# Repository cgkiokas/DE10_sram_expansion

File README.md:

# DE10 SRAM expansion board 
An SRAM expansion board for terasic DE-10 Nano board, with additional flight controller sensors.
Developed to accompany a DE-10 Nano board as a drone flight controller, using [T-CREST's Patmos](https://github.com/t-crest/patmos) processor. 

## Features
* 1Mx32bit SRAM
* 2 x 6-axis IMUs
* Magnetometer
* Barometer
* FTDI for UART output
* 7 GPIO Pins

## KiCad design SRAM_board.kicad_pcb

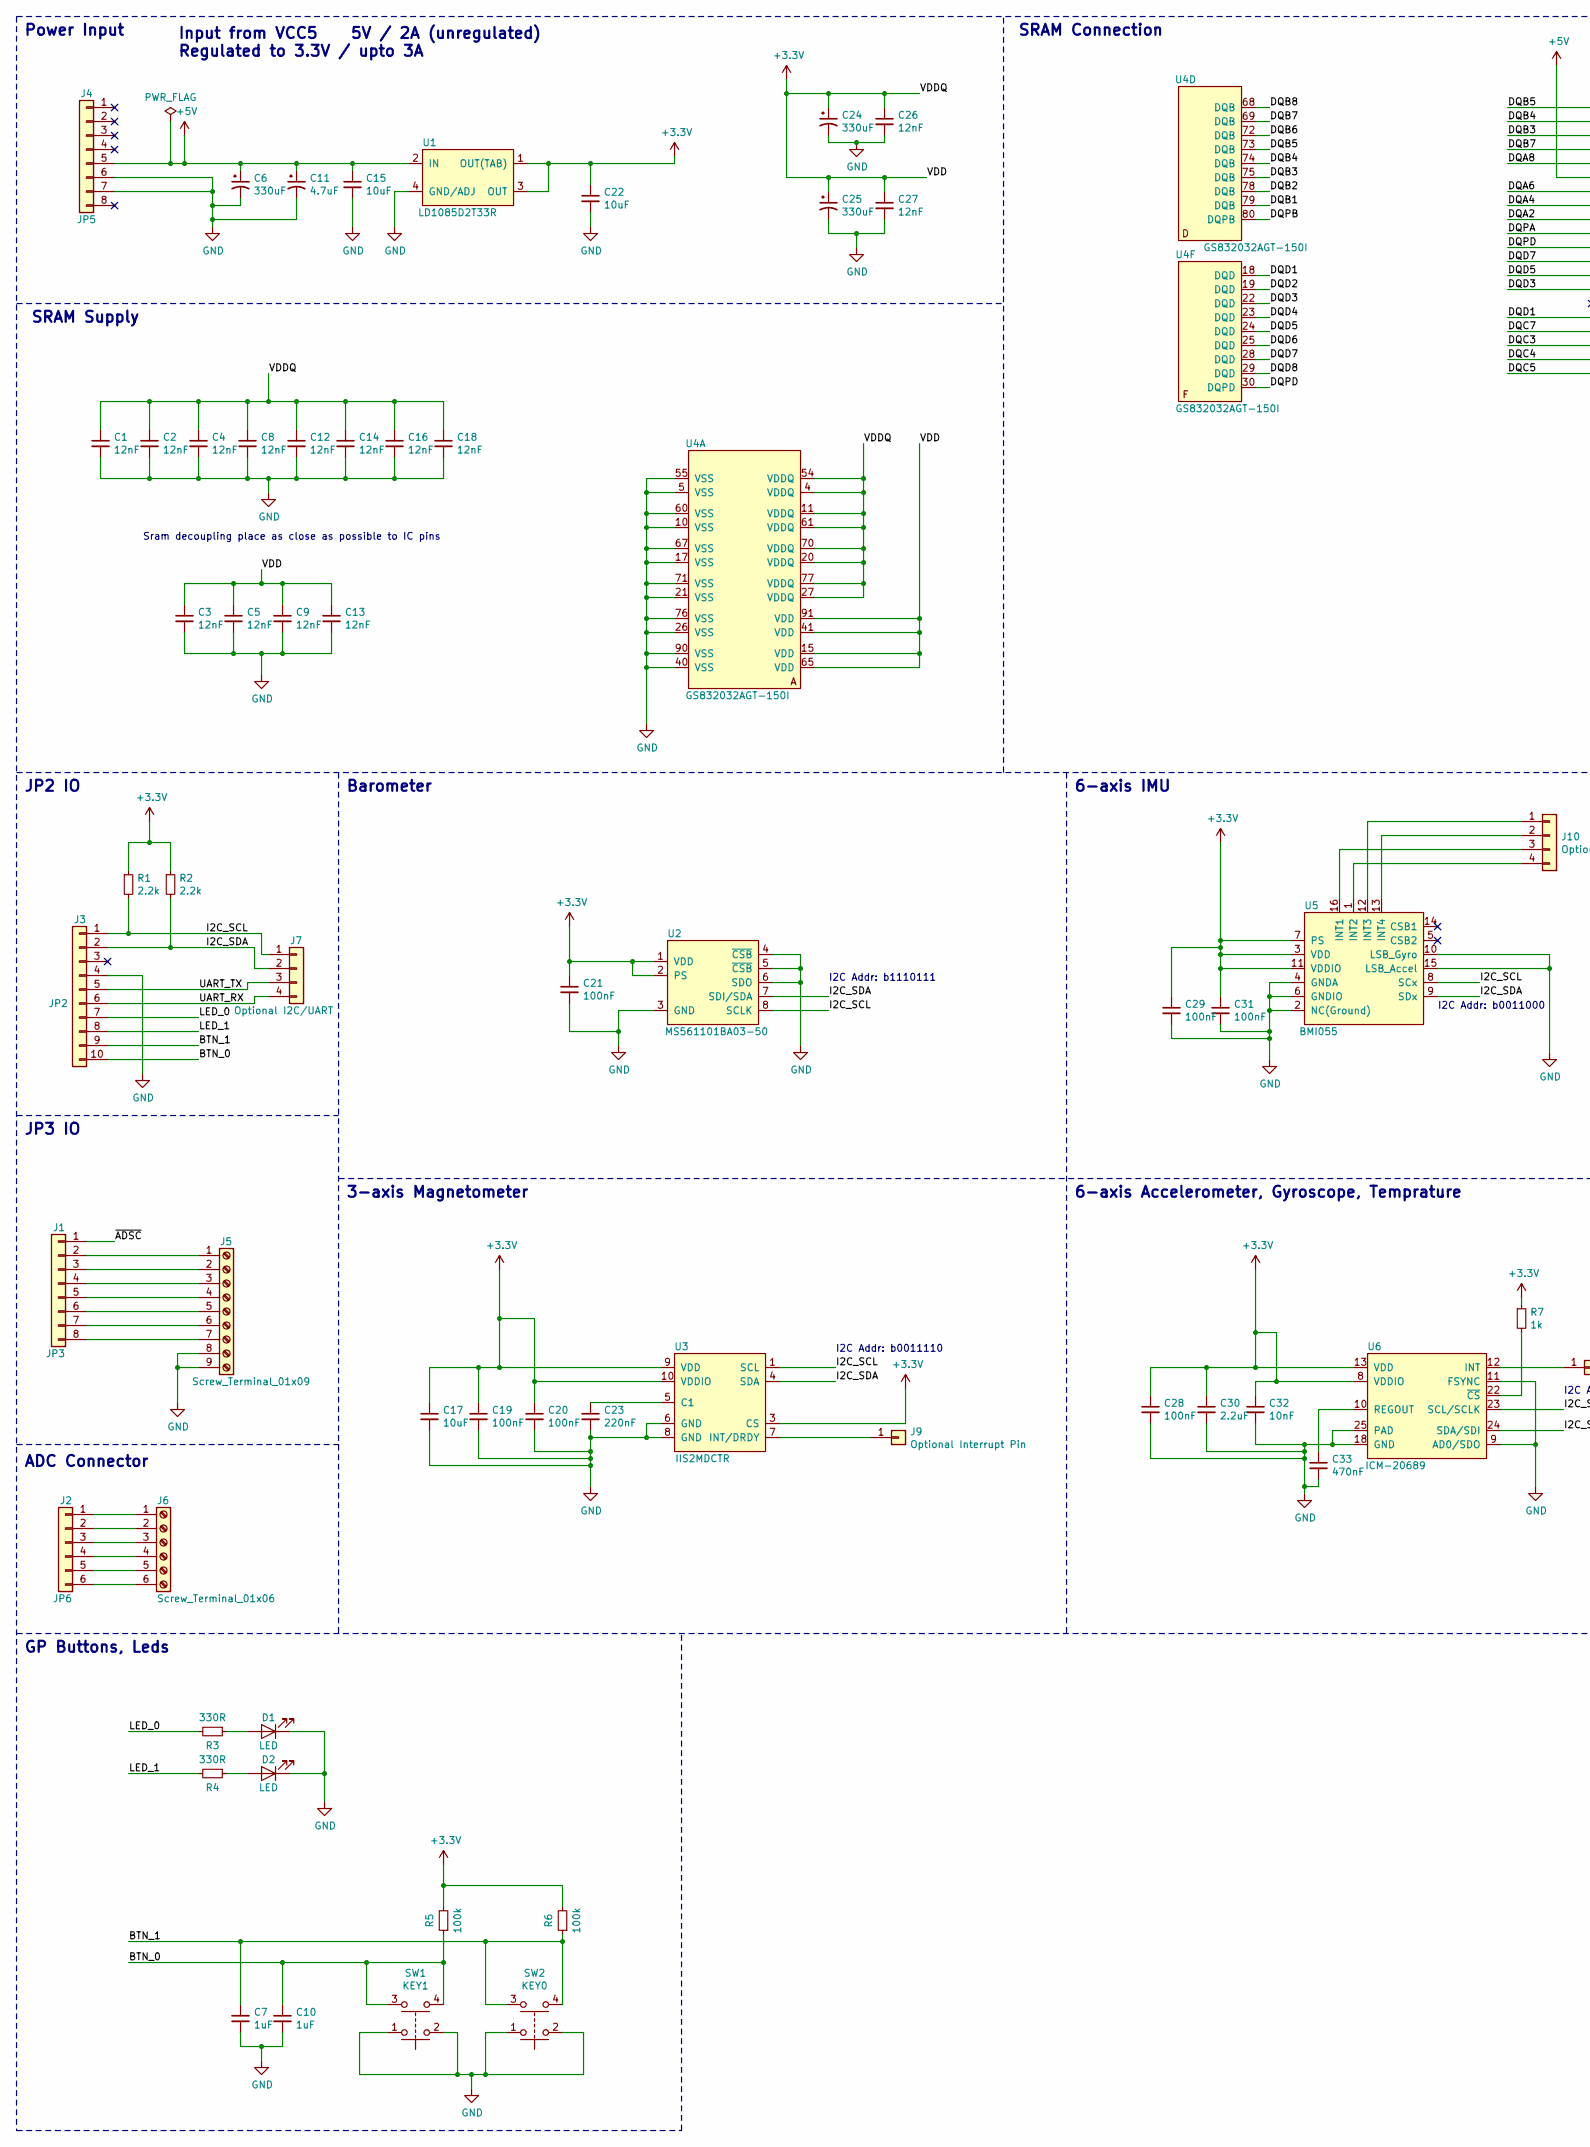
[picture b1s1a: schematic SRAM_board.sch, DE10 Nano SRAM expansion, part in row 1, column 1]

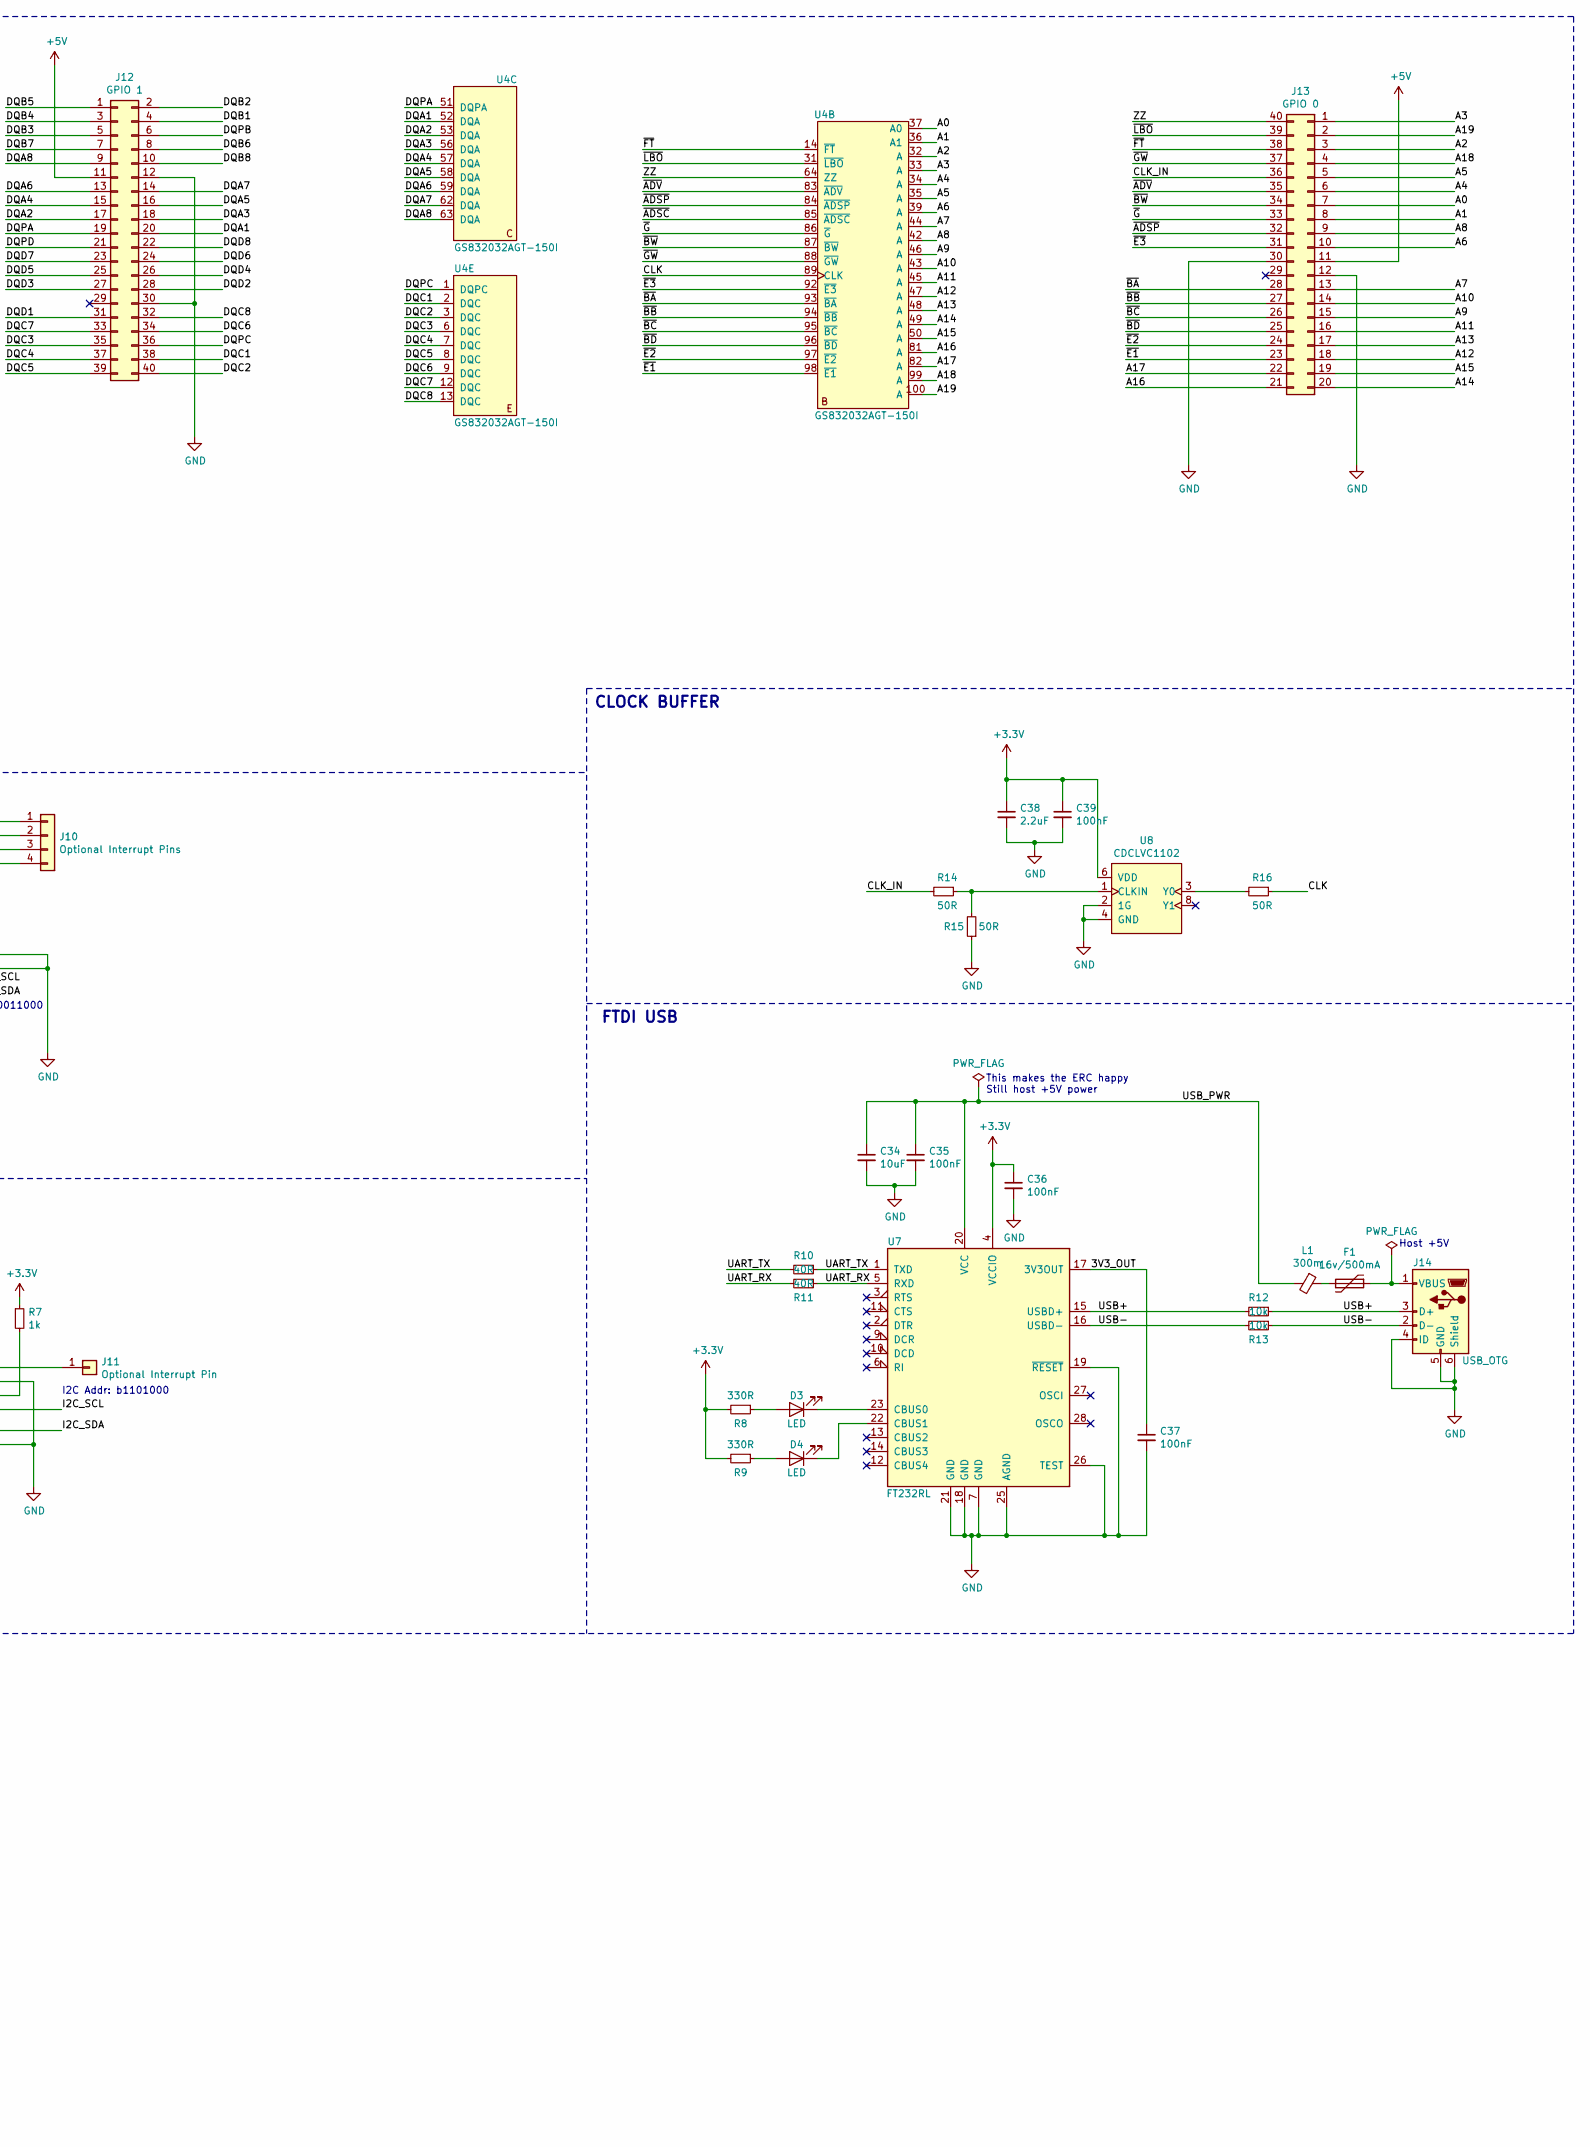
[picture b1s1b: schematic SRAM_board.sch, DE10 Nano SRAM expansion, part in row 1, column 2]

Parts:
C1, C2, C3, C4, C5, C8, C9, C12, C13, C14, C16, C18, C26, C27: 12nF; C_1206_3216Metric_Pad1.42x1.75mm_HandSolder
C6, C24, C25: 330uF; CP_Radial_D6.3mm_P2.50mm
C7, C10: 1uF; C_1206_3216Metric_Pad1.42x1.75mm_HandSolder
C11: 4.7uF; CP_Elec_4x5.8
C15, C17, C22, C34: 10uF; C_1206_3216Metric_Pad1.42x1.75mm_HandSolder
C19, C20, C21, C28, C29, C31, C35, C36, C37, C39: 100nF; C_1206_3216Metric_Pad1.42x1.75mm_HandSolder
C23: 220nF; C_1206_3216Metric_Pad1.42x1.75mm_HandSolder
C30, C38: 2.2uF; C_1206_3216Metric_Pad1.42x1.75mm_HandSolder
C32: 10nF; C_1206_3216Metric_Pad1.42x1.75mm_HandSolder
C33: 470nF; C_1206_3216Metric_Pad1.42x1.75mm_HandSolder
D1, D2, D3, D4: LED; LED_1206_3216Metric_Pad1.42x1.75mm_HandSolder
F1: 16v/500mA; Fuse_1206_3216Metric_Pad1.42x1.75mm_HandSolder
J1: JP3; PinHeader_1x08_P2.54mm_Vertical
J2: JP6; PinHeader_1x06_P2.54mm_Vertical
J3: JP2; PinHeader_1x10_P2.54mm_Vertical
J4: JP5; PinHeader_1x08_P2.54mm_Vertical
J5: Screw_Terminal_01x09; Screw_Terminal_1x09_2.54'_pitch
J6: Screw_Terminal_01x06; Screw_Terminal_1x06_2.54'_pitch
J7: Optional I2C/UART; PinHeader_1x04_P2.54mm_Vertical
J9, J11: Optional Interrupt Pin; PinHeader_1x01_P2.54mm_Vertical
J10: Optional Interrupt Pins; PinHeader_1x04_P2.54mm_Vertical
J12: GPIO 1; PinHeader_2x20_P2.54mm_Vertical
J13: GPIO 0; PinHeader_2x20_P2.54mm_Vertical
J14: USB_OTG; FCI_10118193_0001LF
L1: 300m; L_1206_3216Metric_Pad1.42x1.75mm_HandSolder
R1, R2: 2.2k; R_1206_3216Metric_Pad1.42x1.75mm_HandSolder
R3, R4, R8, R9: 330R; R_1206_3216Metric_Pad1.42x1.75mm_HandSolder
R5, R6: 100k; R_1206_3216Metric_Pad1.42x1.75mm_HandSolder
R7: 1k; R_1206_3216Metric_Pad1.42x1.75mm_HandSolder
R10, R11: 40R; R_1206_3216Metric_Pad1.42x1.75mm_HandSolder
R12, R13: 10k; R_1206_3216Metric_Pad1.42x1.75mm_HandSolder
R14, R15, R16: 50R; R_1206_3216Metric_Pad1.42x1.75mm_HandSolder
SW1: KEY1; LL3301NF065QG
SW2: KEY0; LL3301NF065QG
U1: LD1085D2T33R
U2: MS561101BA03-50
U3: IIS2MDCTR; LGA-12_2x2mm_P0.5mm
U4: GS832032AGT-150I; PQFP-100_14x20mm_P0.65mm
U5: BMI055
U6: ICM-20689
U7: FT232RL; SSOP-28_5.3x10.2mm_P0.65mm
U8: CDCLVC1102; SOIC-8

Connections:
+3V3: C1.1, C2.1, C3.1, C4.1, C5.1, C8.1, C9.1, C12.1, C13.1, C14.1, C16.1, C17.1, C18.1, C19.1, C20.1, C21.1, C22.1, C24.1, C25.1, C26.1, C27.1, C28.1, C29.1, C30.1, C31.1, C32.1, C36.1, C38.1, C39.1, R1.1, R2.1, R5.2, R6.2, R7.1, R8.2, R9.2, U1.1 (OUT(TAB)), U1.3 (OUT), U2.1 (VDD), U2.2 (PS), U3.3 (CS), U3.9 (VDD), U3.10 (VDDIO), U4.4 (VDDQ), U4.11 (VDDQ), U4.15 (VDD), U4.20 (VDDQ), U4.27 (VDDQ), U4.41 (VDD), U4.54 (VDDQ), U4.61 (VDDQ), U4.65 (VDD), U4.70 (VDDQ), U4.77 (VDDQ), U4.91 (VDD), U5.3 (VDD), U5.7 (PS), U5.11 (VDDIO), U6.8 (VDDIO), U6.13 (VDD), U7.4 (VCCIO), U8.6 (VDD)
+5V: C6.1, C11.1, C15.1, J4.5, J12.11, J13.11, U1.2 (IN)
/3V3_OUT: C37.1, U7.17 (3V3OUT)
/A0: J13.7, U4.37 (A0)
/A1: J13.8, U4.36 (A1)
/A2: J13.3, U4.32 (A)
/A3: J13.1, U4.33 (A)
/A4: J13.6, U4.34 (A)
/A5: J13.5, U4.35 (A)
/A6: J13.10, U4.39 (A)
/A7: J13.13, U4.44 (A)
/A8: J13.9, U4.42 (A)
/A9: J13.15, U4.46 (A)
/A10: J13.14, U4.43 (A)
/A11: J13.16, U4.45 (A)
/A12: J13.18, U4.47 (A)
/A13: J13.17, U4.48 (A)
/A14: J13.20, U4.49 (A)
/A15: J13.19, U4.50 (A)
/A16: J13.21, U4.81 (A)
/A17: J13.22, U4.82 (A)
/A18: J13.4, U4.99 (A)
/A19: J13.2, U4.100 (A)
/BTN_0: C10.1, J3.10, R5.1, SW1.3, SW1.4
/BTN_1: C7.1, J3.9, R6.1, SW2.3, SW2.4
/CLK: R16.1, U4.89 (CLK)
/CLK_IN: J13.36, R14.2
/DQA1: J12.20, U4.52 (DQA)
/DQA2: J12.17, U4.53 (DQA)
/DQA3: J12.18, U4.56 (DQA)
/DQA4: J12.15, U4.57 (DQA)
/DQA5: J12.16, U4.58 (DQA)
/DQA6: J12.13, U4.59 (DQA)
/DQA7: J12.14, U4.62 (DQA)
/DQA8: J12.9, U4.63 (DQA)
/DQB1: J12.4, U4.79 (DQB)
/DQB2: J12.2, U4.78 (DQB)
/DQB3: J12.5, U4.75 (DQB)
/DQB4: J12.3, U4.74 (DQB)
/DQB5: J12.1, U4.73 (DQB)
/DQB6: J12.8, U4.72 (DQB)
/DQB7: J12.7, U4.69 (DQB)
/DQB8: J12.10, U4.68 (DQB)
/DQC1: J12.38, U4.2 (DQC)
/DQC2: J12.40, U4.3 (DQC)
/DQC3: J12.35, U4.6 (DQC)
/DQC4: J12.37, U4.7 (DQC)
/DQC5: J12.39, U4.8 (DQC)
/DQC6: J12.34, U4.9 (DQC)
/DQC7: J12.33, U4.12 (DQC)
/DQC8: J12.32, U4.13 (DQC)
/DQD1: J12.31, U4.18 (DQD)
/DQD2: J12.28, U4.19 (DQD)
/DQD3: J12.27, U4.22 (DQD)
/DQD4: J12.26, U4.23 (DQD)
/DQD5: J12.25, U4.24 (DQD)
/DQD6: J12.24, U4.25 (DQD)
/DQD7: J12.23, U4.28 (DQD)
/DQD8: J12.22, U4.29 (DQD)
/DQPA: J12.19, U4.51 (DQPA)
/DQPB: J12.6, U4.80 (DQPB)
/DQPC: J12.36, U4.1 (DQPC)
/DQPD: J12.21, U4.30 (DQPD)
/I2C_SCL: J3.1, J7.1, R1.2, U2.8 (SCLK), U3.1 (SCL), U5.8 (SCx), U6.23 (SCL/SCLK)
/I2C_SDA: J3.2, J7.2, R2.2, U2.7 (SDI/SDA), U3.4 (SDA), U5.9 (SDx), U6.24 (SDA/SDI)
/LED_0: J3.7, R3.2
/LED_1: J3.8, R4.2
/UART_RX: J3.6, J7.4, R11.1, R11.2, U7.5 (RXD)
/UART_TX: J3.5, J7.3, R10.1, R10.2, U7.1 (TXD)
/USB+: J14.3 (D+), R12.1, R12.2, U7.15 (USBD+)
/USB-: J14.2 (D-), R13.1, R13.2, U7.16 (USBD-)
/USB_PWR: C34.1, C35.1, L1.2, U7.20 (VCC)
/ZZ: J13.40, U4.64 (ZZ)
/~ADSC: J1.1, U4.85 (~ADSC)
/~ADSP: J13.32, U4.84 (~ADSP)
/~ADV: J13.35, U4.83 (~ADV)
/~BA: J13.28, U4.93 (~BA)
/~BB: J13.27, U4.94 (~BB)
/~BC: J13.26, U4.95 (~BC)
/~BD: J13.25, U4.96 (~BD)
/~BW: J13.34, U4.87 (~BW)
/~E1: J13.23, U4.98 (~E1)
/~E2: J13.24, U4.97 (~E2)
/~E3: J13.31, U4.92 (~E3)
/~FT: J13.38, U4.14 (~FT)
/~G: J13.33, U4.86 (~G)
/~GW: J13.37, U4.88 (~GW)
/~LBO: J13.39, U4.31 (~LBO)
GND: C1.2, C2.2, C3.2, C4.2, C5.2, C6.2, C7.2, C8.2, C9.2, C10.2, C11.2, C12.2, C13.2, C14.2, C15.2, C16.2, C17.2, C18.2, C19.2, C20.2, C21.2, C22.2, C23.2, C24.2, C25.2, C26.2, C27.2, C28.2, C29.2, C30.2, C31.2, C32.2, C33.2, C34.2, C35.2, C36.2, C37.2, C38.2, C39.2, D1.1 (K), D2.1 (K), J3.4, J4.6, J4.7, J5.8, J5.9, J12.12, J12.30, J13.12, J13.30, J14.4 (ID), J14.5 (GND), J14.6 (Shield), R15.1, SW1.1, SW1.2, SW2.1, SW2.2, U1.4 (GND/ADJ), U2.3 (GND), U2.4 (~CSB), U2.5 (~CSB), U2.6 (SDO), U3.6 (GND), U3.8 (GND), U4.5 (VSS), U4.10 (VSS), U4.17 (VSS), U4.21 (VSS), U4.26 (VSS), U4.40 (VSS), U4.55 (VSS), U4.60 (VSS), U4.67 (VSS), U4.71 (VSS), U4.76 (VSS), U4.90 (VSS), U5.2 (NC(Ground)), U5.4 (GNDA), U5.6 (GNDIO), U5.10 (LSB_Gyro), U5.15 (LSB_Accel), U6.9 (AD0/SDO), U6.11 (FSYNC), U6.18 (GND), U6.25 (PAD), U7.7 (GND), U7.18 (GND), U7.19 (~RESET~), U7.21 (GND), U7.25 (AGND), U7.26 (TEST), U8.2 (1G), U8.4 (GND)
unnamed: C23.1, U3.5 (C1)
unnamed: C33.1, U6.10 (REGOUT)
unnamed: D1.2 (A), R3.1
unnamed: D2.2 (A), R4.1
unnamed: D3.1 (K), U7.23 (CBUS0)
unnamed: D3.2 (A), R8.1
unnamed: D4.1 (K), U7.22 (CBUS1)
unnamed: D4.2 (A), R9.1
unnamed: F1.1, J14.1 (VBUS)
unnamed: F1.2, L1.1
unnamed: J1.2, J5.1
unnamed: J1.3, J5.2
unnamed: J1.4, J5.3
unnamed: J1.5, J5.4
unnamed: J1.6, J5.5
unnamed: J1.7, J5.6
unnamed: J1.8, J5.7
unnamed: J2.1, J6.1
unnamed: J2.2, J6.2
unnamed: J2.3, J6.3
unnamed: J2.4, J6.4
unnamed: J2.5, J6.5
unnamed: J2.6, J6.6
unnamed: J9.1, U3.7 (INT/DRDY)
unnamed: J10.1, U5.12 (INT3)
unnamed: J10.2, U5.13 (INT4)
unnamed: J10.3, U5.16 (INT1)
unnamed: J10.4, U5.1 (INT2)
unnamed: J11.1, U6.12 (INT)
unnamed: R7.2, U6.22 (~CS)
unnamed: R14.1, R15.2, U8.1 (CLKIN)
unnamed: R16.2, U8.3 (Y0)

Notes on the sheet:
Input from VCC5 5V / 2A (unregulated) Regulated to 3.3V / upto 3A
I2C Addr: b1101000
I2C Addr: b0011110
I2C Addr: b0011000
I2C Addr: b1110111
Power Input
SRAM Supply
JP2 IO
SRAM Connection
Barometer
6-axis IMU
3-axis Magnetometer
6-axis Accelerometer, Gyroscope, Temprature
FTDI USB
ADC Connector
JP3 IO
GP Buttons, Leds
Host +5V
This makes the ERC happy Still host +5V power
Sram decoupling place as close as possible to IC pins
CLOCK BUFFER

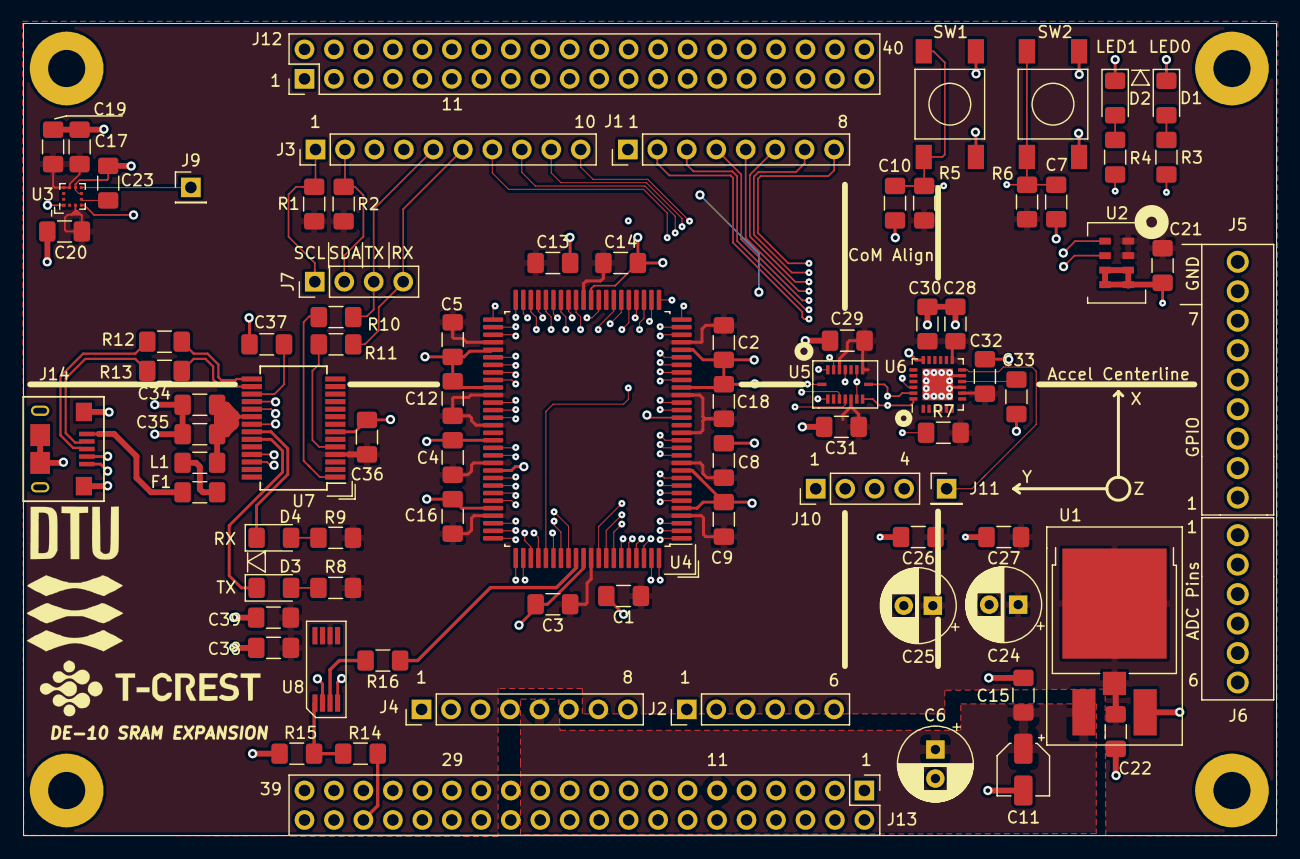
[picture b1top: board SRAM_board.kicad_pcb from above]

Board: 4 copper layers, 108.0 x 70.0 mm, 84 parts (0 on the bottom side), 121 nets.

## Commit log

2019-11-15 cleanup
2019-11-15 readme
2019-11-21 gerbers
2019-11-22 celanup, I2C improvment, SRAM clock buffer
2019-11-28 outputs
2019-11-28 switch sram clock pin
